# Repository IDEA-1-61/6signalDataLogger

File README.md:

# 6signalDataLogger
Un data logger de 6 señales analógicas es un dispositivo que registra los valores de voltaje o corriente de hasta 6 sensores diferentes en una memoria microSD externa.

El data logger puede programarse para iniciar y detener la adquisición de datos.  
Los data loggers de 6 señales analógicas se utilizan para monitorizar y controlar procesos industriales, ambientales, médicos o científicos que requieren
una medición precisa y continua de varios parámetros.

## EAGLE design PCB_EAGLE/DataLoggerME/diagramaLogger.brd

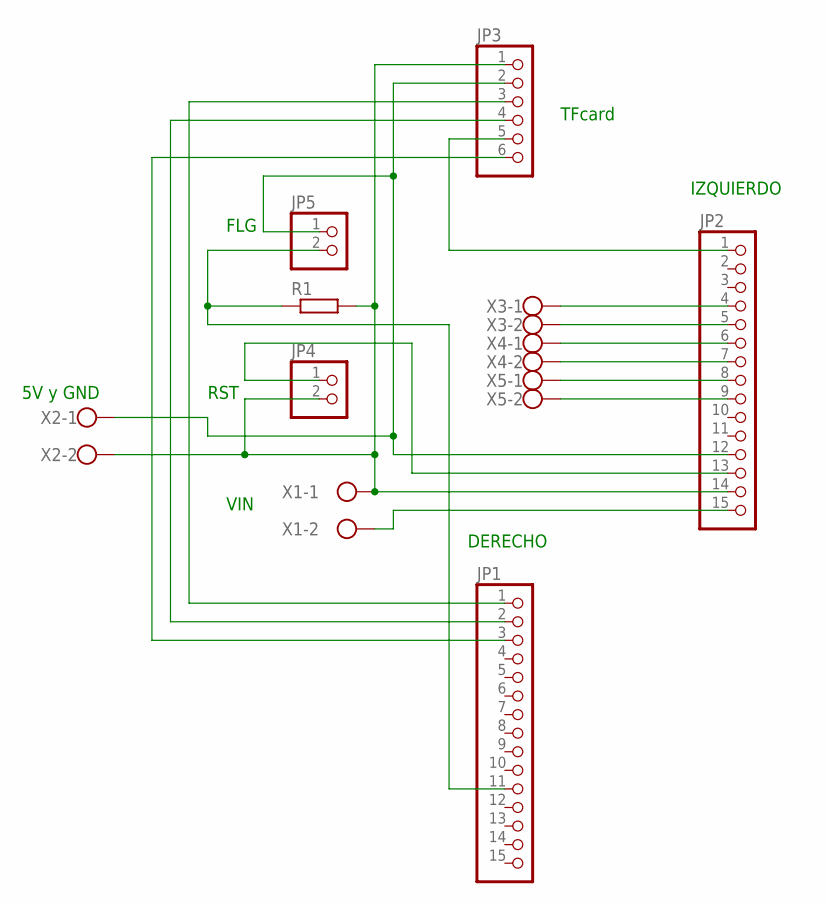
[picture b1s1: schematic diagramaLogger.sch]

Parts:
JP1, JP2: PINHD-1X15; 1X15
JP3: PINHD-1X6; 1X06
JP4, JP5: PINHD-1X2; 1X02
R1: R-EU_0411/12; 0411/12
X1, X2, X3, X4, X5: W237-102

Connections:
unnamed: JP2.14, JP3.1, JP4.2, R1.2, X1.1, X2.2
unnamed: JP2.15, X1.2
unnamed: JP1.3, JP3.6
unnamed: JP2.1, JP3.5
unnamed: JP1.2, JP3.4
unnamed: JP1.1, JP3.3
unnamed: JP2.9, X5.2
unnamed: JP1.11, JP5.2, R1.1
unnamed: JP2.13, JP4.1
unnamed: JP2.8, X5.1
unnamed: JP2.12, JP3.2, JP5.1, X2.1
unnamed: JP2.7, X4.2
unnamed: JP2.6, X4.1
unnamed: JP2.5, X3.2
unnamed: JP2.4, X3.1

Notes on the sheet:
5V y GND
RST
FLG
VIN
IZQUIERDO
DERECHO
TFcard

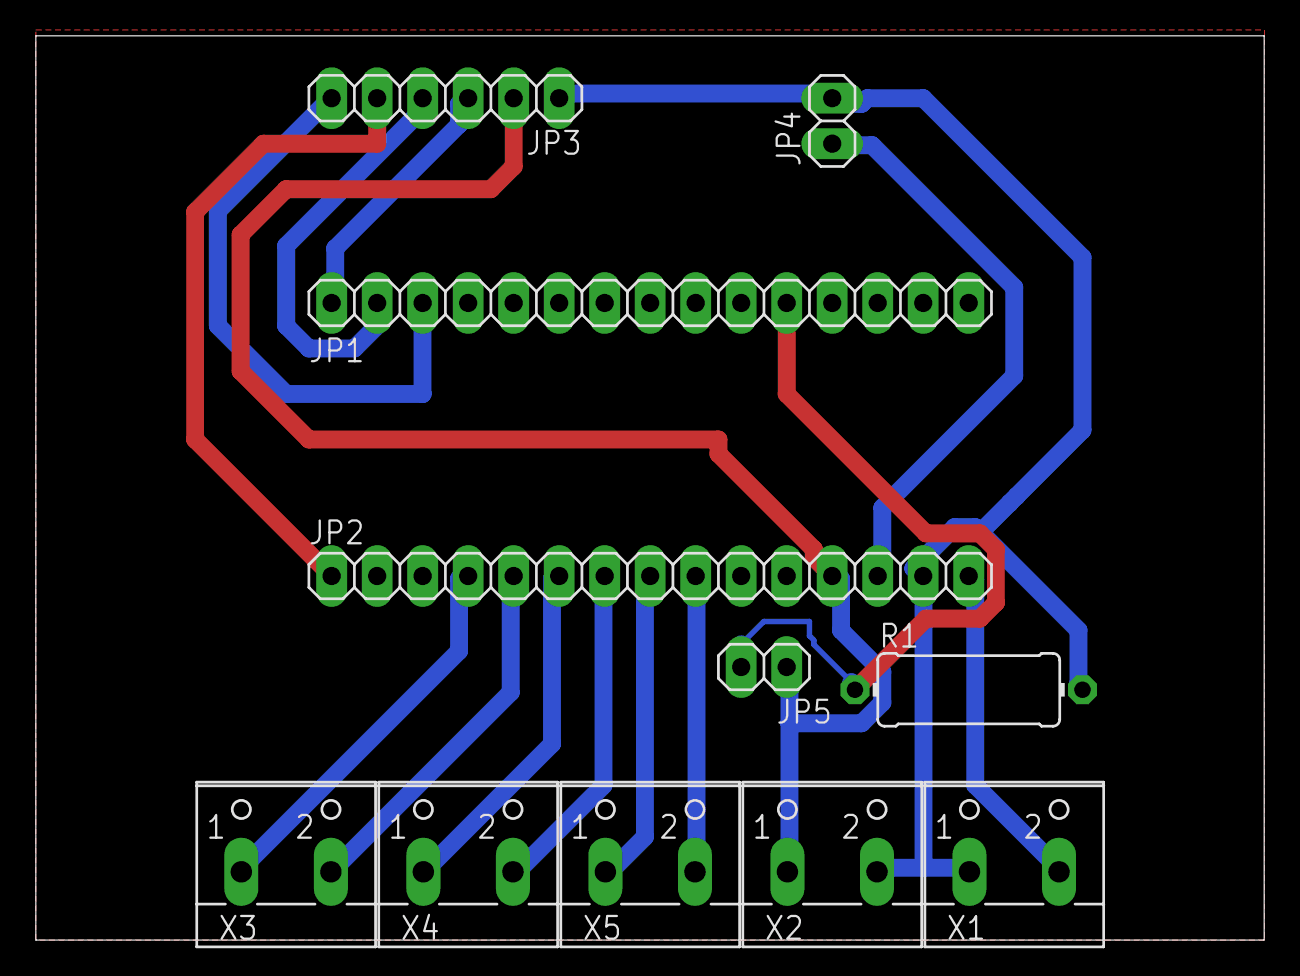
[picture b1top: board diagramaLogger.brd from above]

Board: 2 copper layers, 68.6 x 50.5 mm, 11 parts (0 on the bottom side), 15 nets.

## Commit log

2023-06-18 se agregaron los archivos de la primera version de data logger
2023-06-18 se ha agregado reporte PDF
